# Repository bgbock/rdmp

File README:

More info at http://jaromir.xf.cz/phone/phone1.html

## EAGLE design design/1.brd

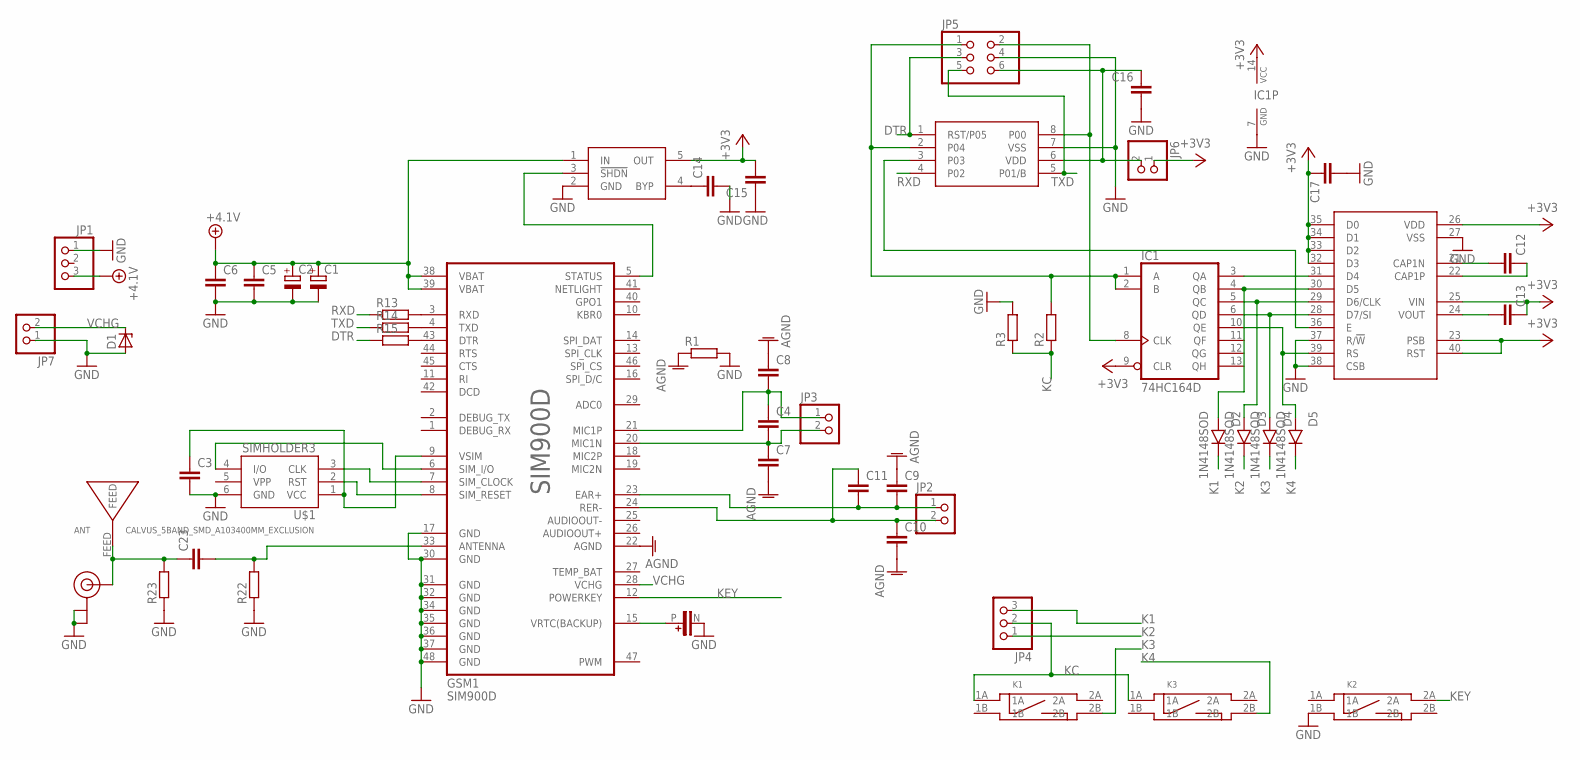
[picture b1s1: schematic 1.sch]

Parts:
ANT: CALVUS_5BAND_SMD_A103400MM_EXCLUSION; CALVUS_5BAND_SMD_A10340_0MM_EXCLUSION
C1, C2: CPOL-EUSMCB; SMC_B
C3, C4, C7, C8, C9, C10, C11, C12, C13, C14, C15, C16, C17: C_0806; R0805
C5, C6: C_1206; R1206
C23: C_0603; 0603
D1: ZENER-DIODESMB; SMB
D2, D3, D4, D5: 1N4148SOD; SOD-80
GSM1: SIM900D
IC1: 74HC164D; SO14
JP1, JP4: PINHD-1X03_2.54-90°; 1X03/90
JP2, JP3: PINHD-1X02_2.00; 1X02M
JP5: PINHD-2X3; 2X03
JP6: PINHD-1X02_2.54-S; 1X02-S
JP7: PINHD-1X02_2.54-90°; 1X02/90
K1, K2, K3: SWITCH_BD_B; SW_SMD2
LCD2: EAGOG_M; EADOGM
R1, R2, R3, R13, R14, R15: R_0805; R0805
R22, R23: R_0603; 0603
U$1: SIMHOLDER3
U$2: LPC810DIP; DIL8
U$3: TC1015; SOT23-5
U$4: SUPERCAP10; SUPERCAP_10
U$10: U.FL

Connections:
+3V3: C13.1, C15.2, C17.1, IC1.9 (CLR), IC1.14 (VCC), JP6.1, LCD2.23 (PSB), LCD2.25 (VIN), LCD2.26 (VDD), LCD2.32 (D3), LCD2.33 (D2), LCD2.34 (D1), LCD2.35 (D0), LCD2.40 (RST), U$3.5 (OUT)
+4.1V: C1.+, C2.+, C5.1, C6.1, GSM1.38 (VBAT), GSM1.39 (VBAT), JP1.3, U$3.1 (IN)
ABC: IC1.1 (A), IC1.2 (B), JP5.1, R2.2, U$2.2 (P04)
AGND: C7.2, C8.1, C9.1, C10.2, GSM1.22 (AGND), R1.1
DTR: JP5.3, R15.1, U$2.1 (RST/P05)
GND: C1.-, C2.-, C3.2, C5.2, C6.2, C14.2, C15.1, C16.2, C17.2, D1.A, GSM1.17 (GND), GSM1.30 (GND), GSM1.31 (GND), GSM1.32 (GND), GSM1.34 (GND), GSM1.35 (GND), GSM1.36 (GND), GSM1.37 (GND), GSM1.48 (GND), IC1.7 (GND), JP1.1, JP5.4, JP7.1, K2.1B, LCD2.27 (VSS), LCD2.37 (R/!W), LCD2.38 (CSB), R1.2, R3.2, R22.1, R23.1, U$1.6 (GND), U$2.7 (VSS), U$3.2 (GND), U$4.N, U$10.P$1 (GND), U$10.P$2 (GND)
K1: D2.K, JP4.3
K2: D3.K, JP4.1
K3: D4.K, K1.2B
K4: D5.K, K3.2B
KC: JP4.2, K1.1A, K3.1A, R2.1, R3.1
KEY: GSM1.12 (POWERKEY), K2.2A
unnamed: GSM1.8 (SIM_RESET), U$1.2 (RST)
unnamed: GSM1.7 (SIM_CLOCK), U$1.3 (CLK)
unnamed: GSM1.6 (SIM_I/O), U$1.4 (I/O)
unnamed: C3.1, GSM1.9 (VSIM), U$1.1 (VCC)
unnamed: GSM1.5 (STATUS), U$3.3 (!SHDN)
unnamed: C14.1, U$3.4 (BYP)
unnamed: C16.1, JP5.6, JP6.2, U$2.6 (VDD)
unnamed: IC1.8 (CLK), JP5.2, U$2.8 (P00)
unnamed: C4.2, C7.1, GSM1.20 (MIC1N), JP3.2
unnamed: C4.1, C8.2, GSM1.21 (MIC1P), JP3.1
unnamed: C9.2, C11.2, GSM1.23 (EAR+), JP2.1
unnamed: C10.1, C11.1, GSM1.24 (RER-), JP2.2
unnamed: D5.A, IC1.10 (QE), LCD2.39 (RS)
unnamed: LCD2.36 (E), U$2.3
unnamed: C13.2, LCD2.24 (VOUT)
unnamed: C12.2, LCD2.21 (CAP1N)
unnamed: C23.2, GSM1.33 (ANTENNA), R22.2
unnamed: C12.1, LCD2.22 (CAP1P)
unnamed: IC1.3 (QA), LCD2.31 (D4)
unnamed: D4.A, IC1.6 (QD), LCD2.28 (D7/SI)
unnamed: GSM1.3 (RXD), R13.2
unnamed: GSM1.4 (TXD), R14.2
unnamed: GSM1.43 (DTR), R15.2
unnamed: D2.A, IC1.4 (QB), LCD2.30 (D5)
unnamed: D3.A, IC1.5 (QC), LCD2.29 (D6/CLK)
unnamed: ANT.FEED, C23.1, R23.2, U$10.P$3 (SIGNAL)
NETLIGHT: GSM1.41 (NETLIGHT)
RXD: R13.1, U$2.4 (P02)
TXD: JP5.5, R14.1, U$2.5 (P01/B)
VCHG: D1.C, GSM1.28 (VCHG), JP7.2
VRTC(BACKUP): GSM1.15 (VRTC(BACKUP)), U$4.P

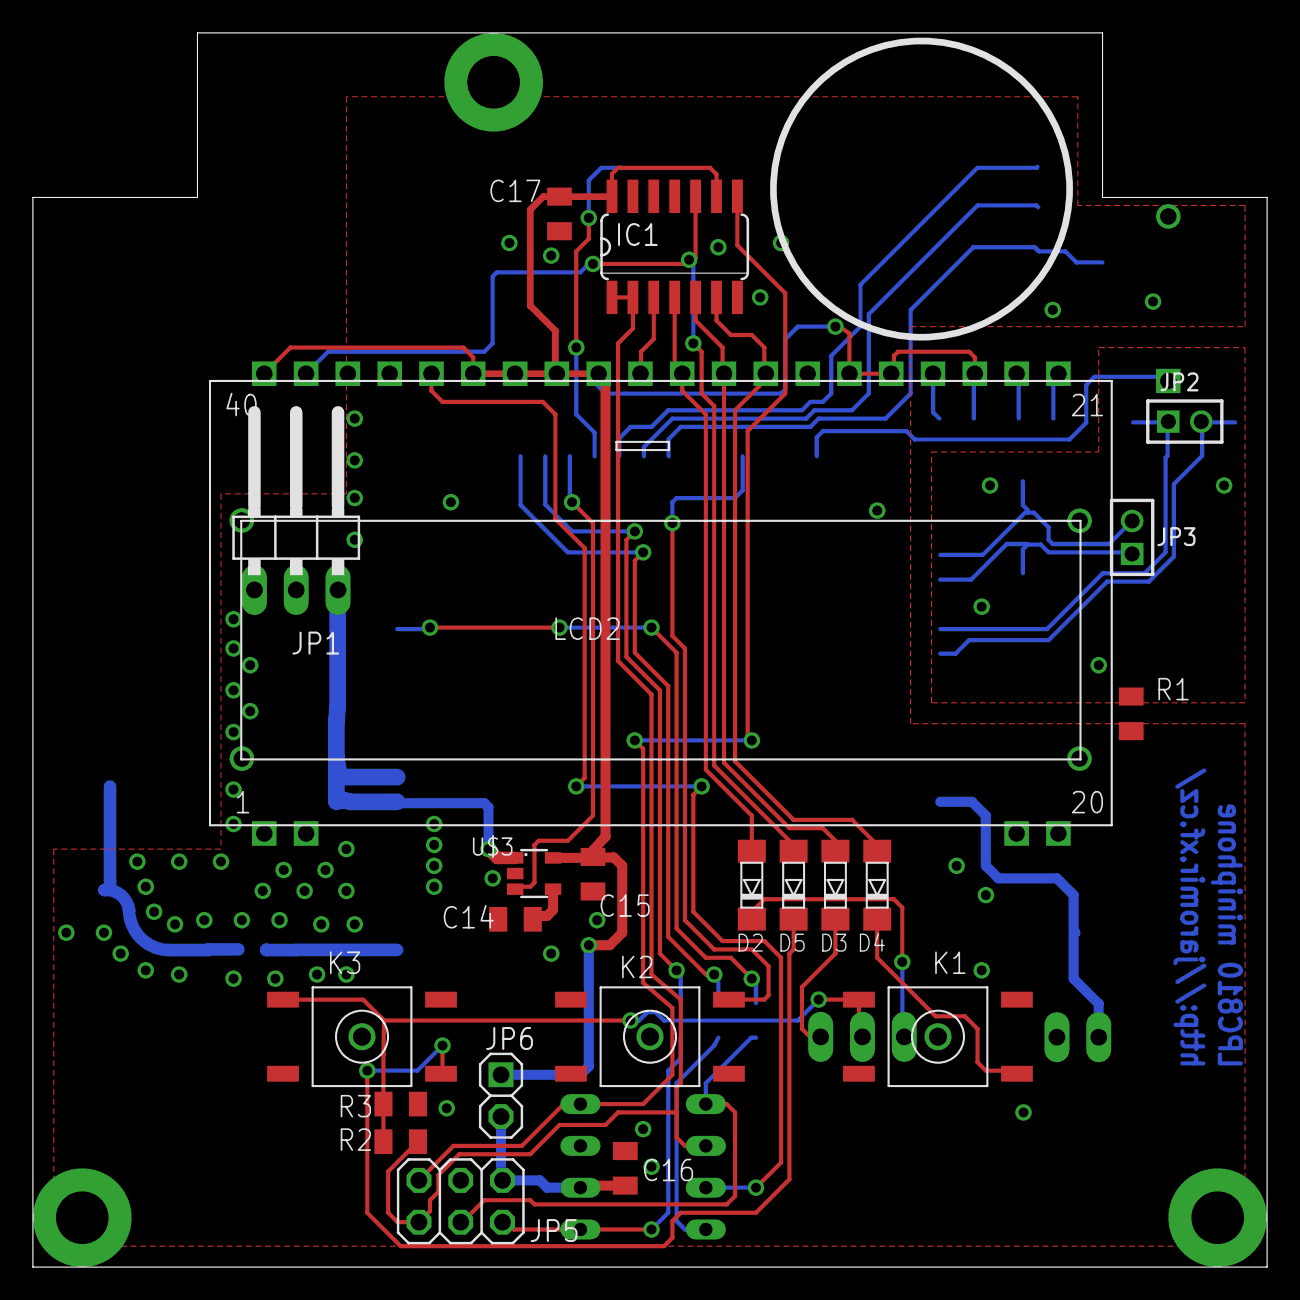
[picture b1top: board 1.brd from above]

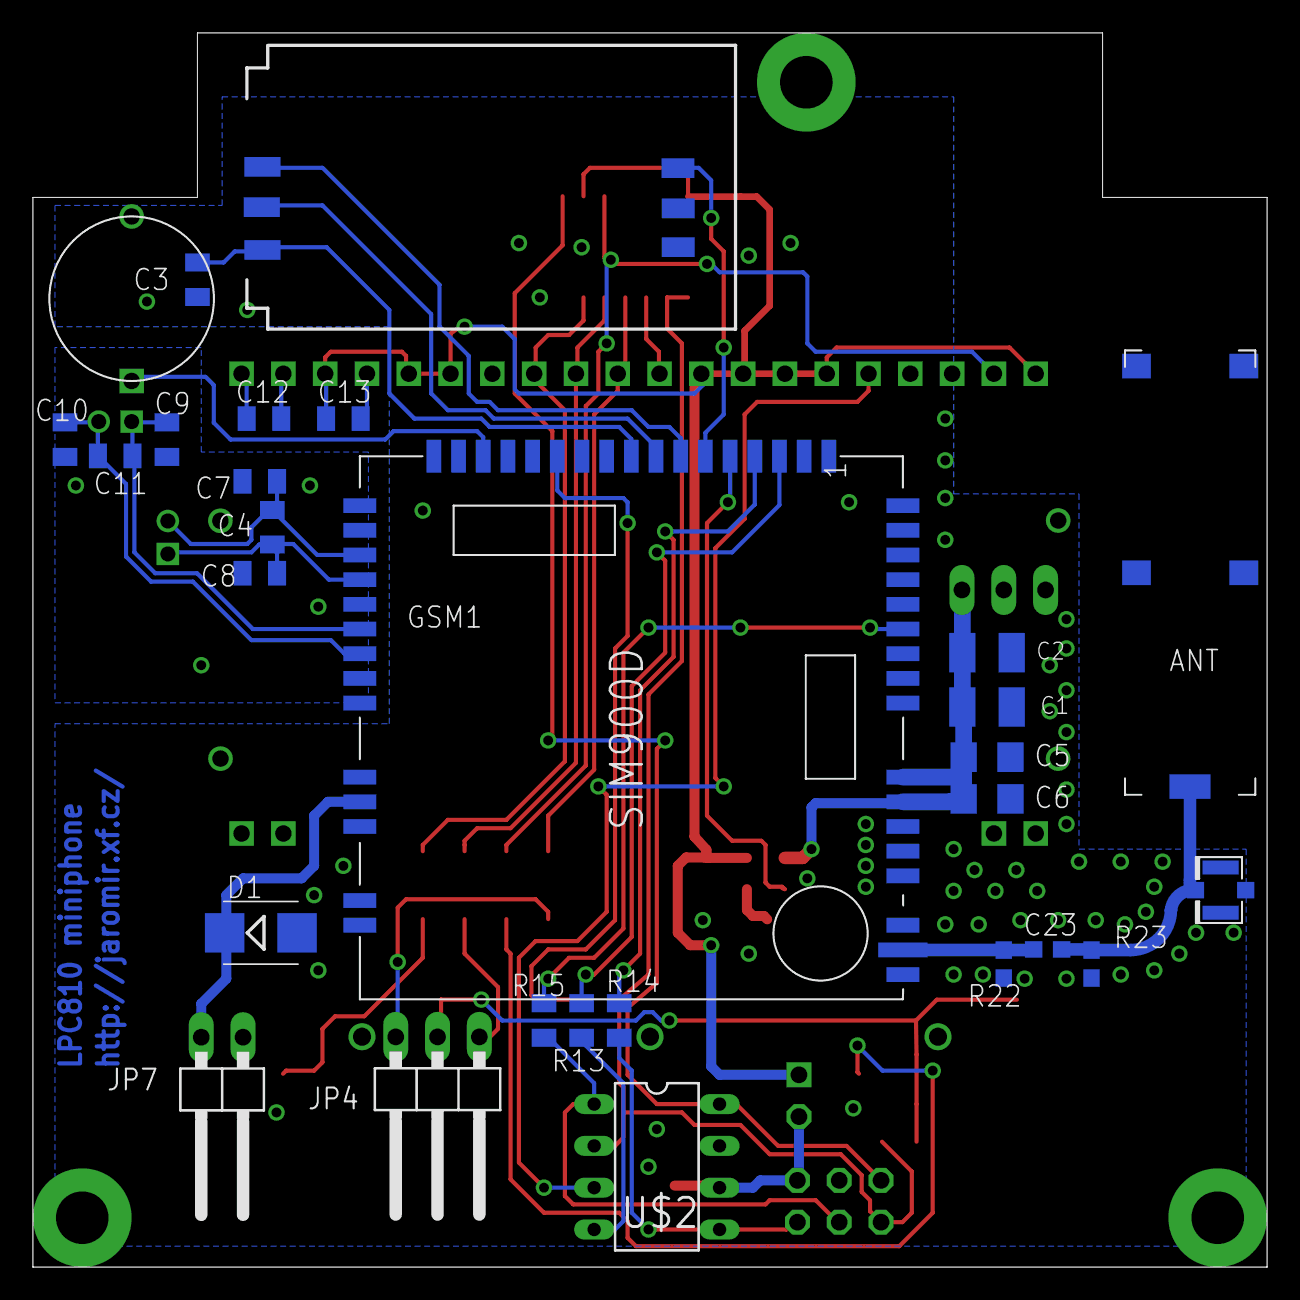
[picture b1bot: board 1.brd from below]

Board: 2 copper layers, 75.0 x 75.0 mm, 50 parts (28 on the bottom side), 42 nets.

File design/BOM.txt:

Qty Value                                Device                               Package                               Parts                    Description                          
2   100u                                 CPOL-EUSMCB                          SMC_B                                 C1, C2                   POLARIZED CAPACITOR, European symbol 
4   1N4148SOD                            1N4148SOD                            SOD-80                                D2, D3, D4, D5                                                
3   1k                                   R_0805                               R0805                                 R13, R14, R15                                                 
1   1n                                   C_0806                               R0805                                 C14                                                           
5   1u                                   C_0806                               R0805                                 C12, C13, C15, C16, C17                                       
1   220n                                 C_0806                               R0805                                 C3                                                            
1   22k                                  R_0805                               R0805                                 R3                                                            
6   22p                                  C_0806                               R0805                                 C4, C7, C8, C9, C10, C11                                      
2   22u                                  C_1206                               R1206                                 C5, C6                                                        
1   2k2                                  R_0805                               R0805                                 R2                                                            
1   74HC164D                             74HC164D                             SO14                                  IC1                      8-bit parallel out SHIFT REGISTER    
1   CALVUS_5BAND_SMD_A103400MM_EXCLUSION A103400MM
1   EAGOG_M                              EAGOG_M_162W                          EADOGM                                LCD2                                                          
1   LPC810DIP                            LPC810DIP                            DIL8                                  U$2                                                           
1   P6KE6V8A                             ZENER-DIODESMB                       SMB                                   D1                       Z-Diode                              
1   SIM900D                              SIM900D                              SIM900D                               GSM1                     maciek@chwarzno.pl                   
1   SIMHOLDER3                           SIMHOLDER3                           SIMHOLDER3                            U$1                                                           
1   SUPERCAP10                           SUPERCAP10                           SUPERCAP_10                           U$4                                                           
3   SWITCH_BD_B                          SWITCH_BD_B                          SW_SMD2                               K1, K2, K3                                                    
1   TC1015                               TC1015                               SOT23-5                               U$3                                                           
1   U.FL                                 U.FL                                 U.FL                                  U$10

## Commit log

2014-03-18 ver 1
    first release
2014-03-18 readme v1
